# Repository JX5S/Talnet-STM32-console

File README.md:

# Talnet STM32 console
Výuková konzole pro vyučování porgramování v C/C++. Uvnitř je STM32F412RET6 mikroprocesor, barevný LCD displej, inerční jednotka BMI160, pípák, tlačítka a joystick.

## Objednávání - plošné spoje
1. Otevřít https://jlcpcb.com/
2. "Add gerber file" a vybrat "GerberA.zip"
3. Změnit "Surface finish" na "LeadFree HASL", pokud nechceme olovo
4. Ostatní nastavení by se měla nastavit podle zip souboru
5. "Save to cart" pro přidání do košíku

6. Opakovat s "GerberB.zip" a objednat

## Objednávání - komponenty z LCSC
1. Otevřít https://lcsc.com/
2. "BOM Tool"
3. Nahrát "LCSC_komponenty.csv"
4. Nad sloupcem množství vybrat v nabídce "Quantity". V souboru jsou sloupce s množstvími pro 1 desku, 5 desek, 10 desek
5. Nad sloupcem "LCSC" vybrat v nabídce "LCSC Part Number"
6. "Next" pro pokračování
7. Zkontrolovat, že je vše na skladě, a kliknout "Add to cart" pro přidání do košíku

8. Pokud něco už není na skladě, je potřeba vybrat náhradní součástky. Většinu součástek by šlo nahradit jednoduše. Dne 30.4.2023 bylo na skladě vše, ale zásoba mikrokontroléru už se krátila - měl by jít nahradit rychlejším, ale dražším STM32F446RET6, bez úpravy desky.
9. Objednat. Pokud první objednáme z JLCPCB, získáme slevu na poštovné

## Objednávání - díly z Aliexpressu
Nabíjecí obvod: https://www.aliexpress.com/item/1005001580997981.html

Displej: https://www.aliexpress.com/item/32843115817.html

BMI160: https://www.aliexpress.com/item/32718555571.html

USB-C: https://www.aliexpress.com/item/1005004598158601.html

## Nastavení programovacího prostředí
1. Stáhneme, nainstalujeme a otevřeme Visual Studio Code
2. V sekci "Extensions" nainstalujeme rozšíření PlatformIO
3. Počkáme na dokončení instalace PlatformIO. Trvá to několik minut
4. File -> Open Folder -> otevřeme nějaký příklad. Měla by být vybrána složka obsahující soubor platformio.ini
5. V sekci "Platformio" otevřeme "Platformio home->Libraries" přidáme do otevřeného projektu knihovnu TFT_eSPI
6. V knihovně (cesta je Příklad/Lib/TFT_eSPI/) zaměníme soubor user_setup.h se souborem z tohoto repositáře. Tento soubor nastaví, jaký konkrétní displej máme. Je možné, že bude nutné mírně upravit pro jiné displeje, i když budou vypadat stejně
7. V sekci "Platformio -> Project tasks" spustíme "Upload" pro nahrání programu

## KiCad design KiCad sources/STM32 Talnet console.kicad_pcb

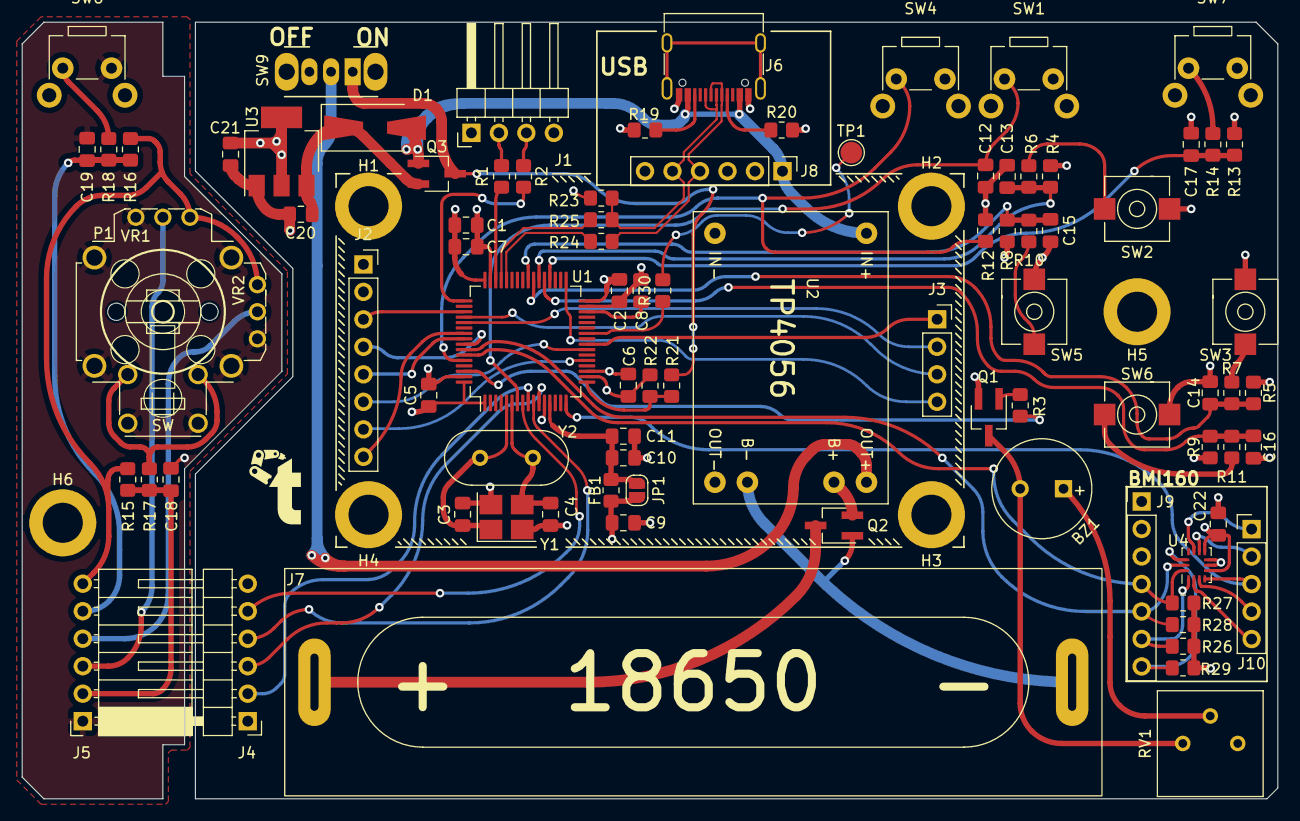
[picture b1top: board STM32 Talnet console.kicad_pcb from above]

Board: 4 copper layers, 116.0 x 71.8 mm, 93 parts (0 on the bottom side), 65 nets.

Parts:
BZ1: Buzzer; MagneticBuzzer_PUI_AT-0927-TT-6-R
C1, C9, C10, C20, C21: 10u; C_0805_2012Metric_Pad1.18x1.45mm_HandSolder
C2, C5, C6, C7, C11, C12, C13, C14, C15, C16, C17, C18, C19, C22: 100n; C_0805_2012Metric_Pad1.18x1.45mm_HandSolder
C3, C4: 8p; C_0805_2012Metric_Pad1.18x1.45mm_HandSolder
C8: 2.2u; C_0805_2012Metric_Pad1.18x1.45mm_HandSolder
D1: SS14; D_SMA-SMB_Universal_Handsoldering
FB1: 120R; R_0805_2012Metric_Pad1.20x1.40mm_HandSolder
H1, H2, H3, H4, H5, H6: M2; M2 solder nut
J1: Conn_01x04_Male; PinHeader_1x04_P2.54mm_Horizontal
J2: LCD; PinSocket_1x08_P2.54mm_Vertical
J3: Mech; PinSocket_1x04_P2.54mm_Vertical
J4: Joy_P; PinHeader_1x06_P2.54mm_Horizontal
J5: Joy_S; PinSocket_1x06_P2.54mm_Horizontal
J6: USB_C_Receptacle_USB2.0; USB_C_Receptacle_G-Switch_GT-USB-7010ASV
J7: BConn; 18650 MYOUNG
J8: USB_breakout; PinHeader_1x06_P2.54mm_Vertical
J9: Conn_01x07; PinHeader_1x07_P2.54mm_Vertical
J10: Conn_01x05; PinHeader_1x05_P2.54mm_Vertical
JP1: Jumper_2_Open; SolderJumper-2_P1.3mm_Open_RoundedPad1.0x1.5mm
P1: Joystick_RKJXV122400R; Joystic_ALPSALPINE_RKJXV122400D
Q1: SI2302; SOT-23W_Handsoldering
Q2, Q3: CJ2302; SOT-23W_Handsoldering
R1, R2, R24, R25: 22R; R_0805_2012Metric_Pad1.20x1.40mm_HandSolder
R3, R23: 1K5; R_0805_2012Metric_Pad1.20x1.40mm_HandSolder
R4, R5, R8, R9, R12, R13, R15, R16: 10k; R_0805_2012Metric_Pad1.20x1.40mm_HandSolder
R6, R7, R10, R11, R14, R17, R18, R30: 1k; R_0805_2012Metric_Pad1.20x1.40mm_HandSolder
R19, R20: 5K1; R_0805_2012Metric_Pad1.20x1.40mm_HandSolder
R21, R22: 100K; R_0805_2012Metric_Pad1.20x1.40mm_HandSolder
R26, R27, R28, R29: 4K7; R_0805_2012Metric_Pad1.20x1.40mm_HandSolder
RV1: 10k; Potentiometer_Bourns_3386P_Vertical
SW1, SW4: SW_Push; SKHHLNA010
SW2: SW_Up; Switch_ALPSALPINE_SKPMAME010
SW3: SW_Right; Switch_ALPSALPINE_SKPMAME010
SW5: SW_Left; Switch_ALPSALPINE_SKPMAME010
SW6: SW_Down; Switch_ALPSALPINE_SKPMAME010
SW7: SW_Rsh; SKHHLNA010
SW8: SW_Lsh; SKHHLNA010
SW9: SW_SPDT; SW_CuK_OS102011MA1QN1_SPDT_Angled
TP1: TestPoint; TestPoint_Pad_D2.0mm
U1: STM32F412RETx; LQFP-64_10x10mm_P0.5mm
U2: TP4056; TP4056+prot
U3: AMS1117-3.3; SOT-223-3_TabPin2
U4: BMI160; Bosch_LGA-14_3x2.5mm_P0.5mm
Y1: 25MHz; Crystal_SMD_3225-4Pin_3.2x2.5mm_HandSoldering
Y2: 25MHz; Crystal_HC49-4H_Vertical

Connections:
+3.3V: C1.1, C2.1, C5.1, C6.1, C7.1, C9.1, C21.1, C22.1, FB1.2, J1.1, J2.1, J4.6, J9.2, JP1.2 (B), R4.2, R5.2, R8.2, R9.2, R13.2, R23.1, R26.1, R27.1, R28.1, R29.1, RV1.1, SW4.2, U1.1 (VBAT), U1.19 (VDD), U1.32 (VDD), U1.48 (VDD), U1.64 (VDD), U3.2 (VO), U4.5 (VDDIO), U4.8 (VDD)
+3.3VA: C10.1, C11.1, FB1.1, JP1.1 (A), U1.13 (VDDA)
+3.3VP: J5.6, P1.3 (A), P1.4 (A), R15.2, R16.2
/Gyro/CS: J9.6, R26.2, U4.1 (SDO)
/Gyro/INT2: J10.2, U4.9 (INT2)
/Gyro/OCS: J10.1, U4.10 (OCSB)
/Gyro/SA0: J9.7, R29.2, U4.12 (CSB)
/Gyro/SCX: J10.4, U4.3 (ASCx)
/Gyro/SDX: J10.5, U4.2 (ASDx)
/OSC_IN: C3.2, U1.5 (PH0), Y1.1, Y2.1
/OSC_OUT: C4.2, U1.6 (PH1), Y1.3, Y2.2
/Power/_USB_D+: J6.A6 (D+), J6.B6 (D+), J8.5, R23.2, R25.1
/Power/_USB_D-: J6.A7 (D-), J6.B7 (D-), J8.4, R24.2
/SD_CS: J3.1, U1.24 (PC4)
/SD_MISO: J3.3, U1.52 (PC11)
/SD_MOSI: J3.2, U1.53 (PC12)
/SD_SCK: J3.4, U1.33 (PB12)
/SWCLK: R2.1, U1.49 (PA14)
/SWDIO: R1.2, U1.46 (PA13)
/USB_D+: R25.2, U1.45 (PA12)
/USB_D-: R24.1, U1.44 (PA11)
/VBAT_ADC: R21.2, R22.1, U1.17 (PA3)
/Vstupy/VRx: J5.3, P1.2 (D)
/Vstupy/VRy: J5.4, P1.5 (D)
BOOT0: R12.1, SW4.1, U1.60 (BOOT0)
BTN_DOWN: R9.1, U1.37 (PC6)
BTN_LEFT: R8.1, U1.40 (PC9)
BTN_RIGHT: R5.1, U1.39 (PC8)
BTN_UP: R4.1, U1.38 (PC7)
GND: C1.2, C2.2, C3.1, C4.1, C5.2, C6.2, C7.2, C8.2, C9.2, C10.2, C11.2, C12.2, C13.2, C14.2, C15.2, C16.2, C17.2, C20.2, C21.2, C22.2, J1.4, J2.2, J4.1, J6.A1 (GND), J6.A12 (GND), J6.B1 (GND), J6.B12 (GND), J8.2, J9.3, Q1.2 (S), R12.2, R19.2, R20.2, R22.2, SW1.2, SW2.2, SW3.2, SW5.2, SW6.2, SW7.2, U1.12 (VSSA), U1.18 (VSS), U1.31 (VSS), U1.47 (VSS), U1.63 (VSS), U2.2 (In-), U2.6 (OUT-), U3.1 (GND), U4.6 (GNDIO), U4.7 (GND), Y1.2, Y1.4
GND2: C18.2, C19.2, J5.1, P1.1 (B), P1.6 (B), P1.SH, P1.b, P1.d, SW8.2
LCD_BLK: J2.8, U1.55 (PB3)
LCD_CS: J2.3, U1.51 (PC10)
LCD_DC: J2.5, U1.56 (PB4)
LCD_MOSI: J2.6, U1.23 (PA7)
LCD_RES: J2.4, U1.57 (PB5)
LCD_SCK: J2.7, U1.21 (PA5)
NRST: C12.1, SW1.1, U1.7 (NRST)
unnamed: BZ1.2 (+), Q1.3 (D), RV1.3
unnamed: BZ1.1 (-), RV1.2
unnamed: C20.1, D1.1 (K), Q3.2 (S), U3.3 (VI)
unnamed: J1.2, R1.1
unnamed: J1.3, R2.2
unnamed: C18.1, J5.2, R15.1, R17.1
unnamed: C19.1, J5.5, R16.1, R18.1
unnamed: J6.A5 (CC1), R20.1
unnamed: J6.B5 (CC2), R19.1
unnamed: J7.1, Q2.3 (D)
unnamed: J7.2, Q2.1 (G), U2.5 (Bat-)
unnamed: P1.a, P1.c, R17.2
unnamed: Q1.1 (G), R3.2
unnamed: Q2.2 (S), U2.4 (Bat+)
unnamed: Q3.3 (D), R21.1, SW9.1 (A)
unnamed: R6.2, SW2.1
unnamed: R7.2, SW3.1
unnamed: R10.2, SW5.1
unnamed: R11.2, SW6.1
unnamed: R14.2, SW7.1
unnamed: R18.2, SW8.1
unnamed: R30.2, TP1.1
unnamed: SW9.2 (B), U2.3 (OUT+)
unnamed: R30.1, U1.26 (PB0)
unnamed: R3.1, U1.62 (PB9)
unnamed: C8.1, U1.30 (VCAP_1)
VBUS: D1.2 (A), J6.A4 (VBUS), J6.A9 (VBUS), J6.B4 (VBUS), J6.B9 (VBUS), J8.1, Q3.1 (G), U2.1 (In+)

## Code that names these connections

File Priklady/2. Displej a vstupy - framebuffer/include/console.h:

#define Console_LED           PB0

#define Console_Buzzer        PB9

#define Console_BTN_RShoulder PB15
#define Console_BTN_LShoulder PC0
#define Console_BTN_Left      PC9
#define Console_BTN_Right     PC8
#define Console_BTN_Up        PC7
#define Console_BTN_Down      PC6

#define Console_Joy_BTN       PC1
#define Console_Joy_X         PC3
#define Console_Joy_Y         PC2

#define Console_TFT_BLK       PB3
#define Console_TFT_MISO      PC11
#define Console_TFT_MOSI      PC12
#define Console_TFT_SCK       PB12
#define Console_TFT_CS        PC10
#define Console_TFT_RST       PB5
#define Console_TFT_DC        PB4

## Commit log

2023-04-30 Create Priklady
2023-04-30 Create a
2023-05-06 Update README.md
    Added photos
2023-05-06 jednoduše
2023-05-08 Create LICENSE
2023-06-02 Update pong
    Přidány komentáře
